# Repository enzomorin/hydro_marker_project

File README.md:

# hydro_marker_project

A beacon placed in small rivers to measure flooding risk, hydric stress, or normal conditions — built for the **Olympiads of Engineering Sciences**.

---

## Project overview

Each marker is a waterproof device deployed in a river. It measures water level, pressure, temperature, and battery voltage, then transmits the data via radio to a ground antenna. The antenna forwards the data to the API server, which stores it and makes it available to a dashboard and a mobile alert application.

---

## Repository structure

```
hydro_marker_project/
│
├── docs/           Documentation, source references, notes, and diagrams
│
├── app/            Dashboard application
│                   Receives data from the ground antenna, processes it,
│                   and sends it to the API. Also includes a companion app
│                   that sends alerts when a nearby marker detects potential
│                   flooding or hydric stress.
│
├── firmware/       Embedded code
│                   MCU code for the marker (sensor reading + radio transmission)
│                   and code for the ground station (receiving + forwarding frames).
│
├── hardware/       PCB design files (KiCad)
│                   Optimised circuit board for the markers — reduces electrical
│                   noise and improves efficiency.
│
├── server/         API server
│                   FastAPI + SQLite REST API that stores marker locations
│                   and all associated measurement data.
│
├── site/           Promotional website
│                   Presents the product and its specifications.
│                   Also displays live marker data and locations on a map.
│
└── tools/          Development utilities
                    Scripts and helpers that speed up development across
                    all parts of the project.
```

---

## Quick start

To run the API server locally, see [`server/README.md`](server/README.md).

---

## Tech used overview

| Component | Technology |
|---|---|
| API server | Python, FastAPI, SQLite |
| Firmware | C++ (MCU), PlatfromIO IDE |
| PCB design | KiCad |
| Dashboard | Electron, Javascript |
| Website | HTML, CSS, Javascript |

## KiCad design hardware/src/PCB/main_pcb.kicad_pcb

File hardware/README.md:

# HydroVinci — PCB Design

> Compact, low-power PCB for the HydroVinci marker system. Designed in KiCad 10, built around the Seeed XIAO nRF52840 Plus.

---

## Table of Contents

- [Overview](#overview)
- [Hardware Summary](#hardware-summary)
- [Prerequisites](#prerequisites)
- [Opening the Project](#opening-the-project)
- [Manufacturing](#manufacturing)
- [Design Notes](#design-notes)
- [Tech used](#tech-used)

---

## Overview

This repository contains the full KiCad design files for the HydroVinci PCB. The board integrates all electronics required by the marker into a single compact PCB, replacing a wired prototype with a manufacturable solution.

The design targets low quiescent current for battery-powered field deployment, with switchable power rails for each peripheral.

---

## Hardware Summary

| Component | Description |
|-----------|-------------|
| MCU | Seeed XIAO nRF52840 Plus (BLE 5.0, nRF52840) |
| Power | LiPo battery input, 12V boost (Adafruit TPS61040) |
| Pressure sensor | DFRobot KIT0139 submersible 4-20mA, converted via SEN0262 |
| Environmental | AZ-Delivery GY-BME280 (temperature, humidity, pressure) |
| Hall effect | Digital Hall sensor via BSS84 high-side switch |
| Data logging | SparkFun OpenLog DEV-13712 (microSD, UART) |
| RF | CC1101 sub-GHz radio module |
| Power switching | BSS138 + BSS84 MOSFET pairs (3.3V and 12V rails) |
| Indicators | Passive buzzer, 2× tactile buttons |

---

## Prerequisites

- [KiCad](https://www.kicad.org/) `>= 10.0`

No additional dependencies. All custom symbols and footprints are included in the repository under `src/PCB/libraries/`.

---

## Opening the Project

1. Clone the repository
   ```bash
   git clone https://github.com/your-org/hydrovinci-pcb.git
   ```

2. Open KiCad and select **File → Open Project**

3. Navigate to `src/PCB/main_pcb.kicad_pro` and open it

From the KiCad project manager you can then open:
- **Schematic Editor** — for the electrical design and component wiring
- **PCB Editor** — for the physical board layout and copper routing

---

## Manufacturing

Gerber files are required to manufacture the board. To generate them from KiCad:

1. Open the PCB Editor (`main_pcb.kicad_pcb`)
2. Go to **File → Fabrication Outputs → Gerbers**
3. Select all required layers and export

The generated Gerbers can be uploaded directly to:
- [JLCPCB](https://jlcpcb.com) — recommended for low-cost prototyping
- [PCBway](https://www.pcbway.com) — recommended for higher quantities

> **Recommended specs:** 2-layer, 1oz copper.

---

## Design Notes

- All GPIO outputs include 100Ω series resistors for noise immunity
- The 12V rail (KIT0139 sensor loop) is switched via a BSS138 + BSS84 MOSFET pair — Vgs is clamped to −6V by R20 to stay within BSS84 absolute maximum ratings
- The EN pin of the boost converter is pulled to GND via R7 (100kΩ) to ensure the 12V rail is off during boot and reset
- The SEN0262 output capacitor (C14) must be rated ≥ 25V (ceramic X5R/X7R, 0805)
- I2C pull-ups R3/R4 (10kΩ) may be omitted if the BME280 module already includes them

---

## Tech used

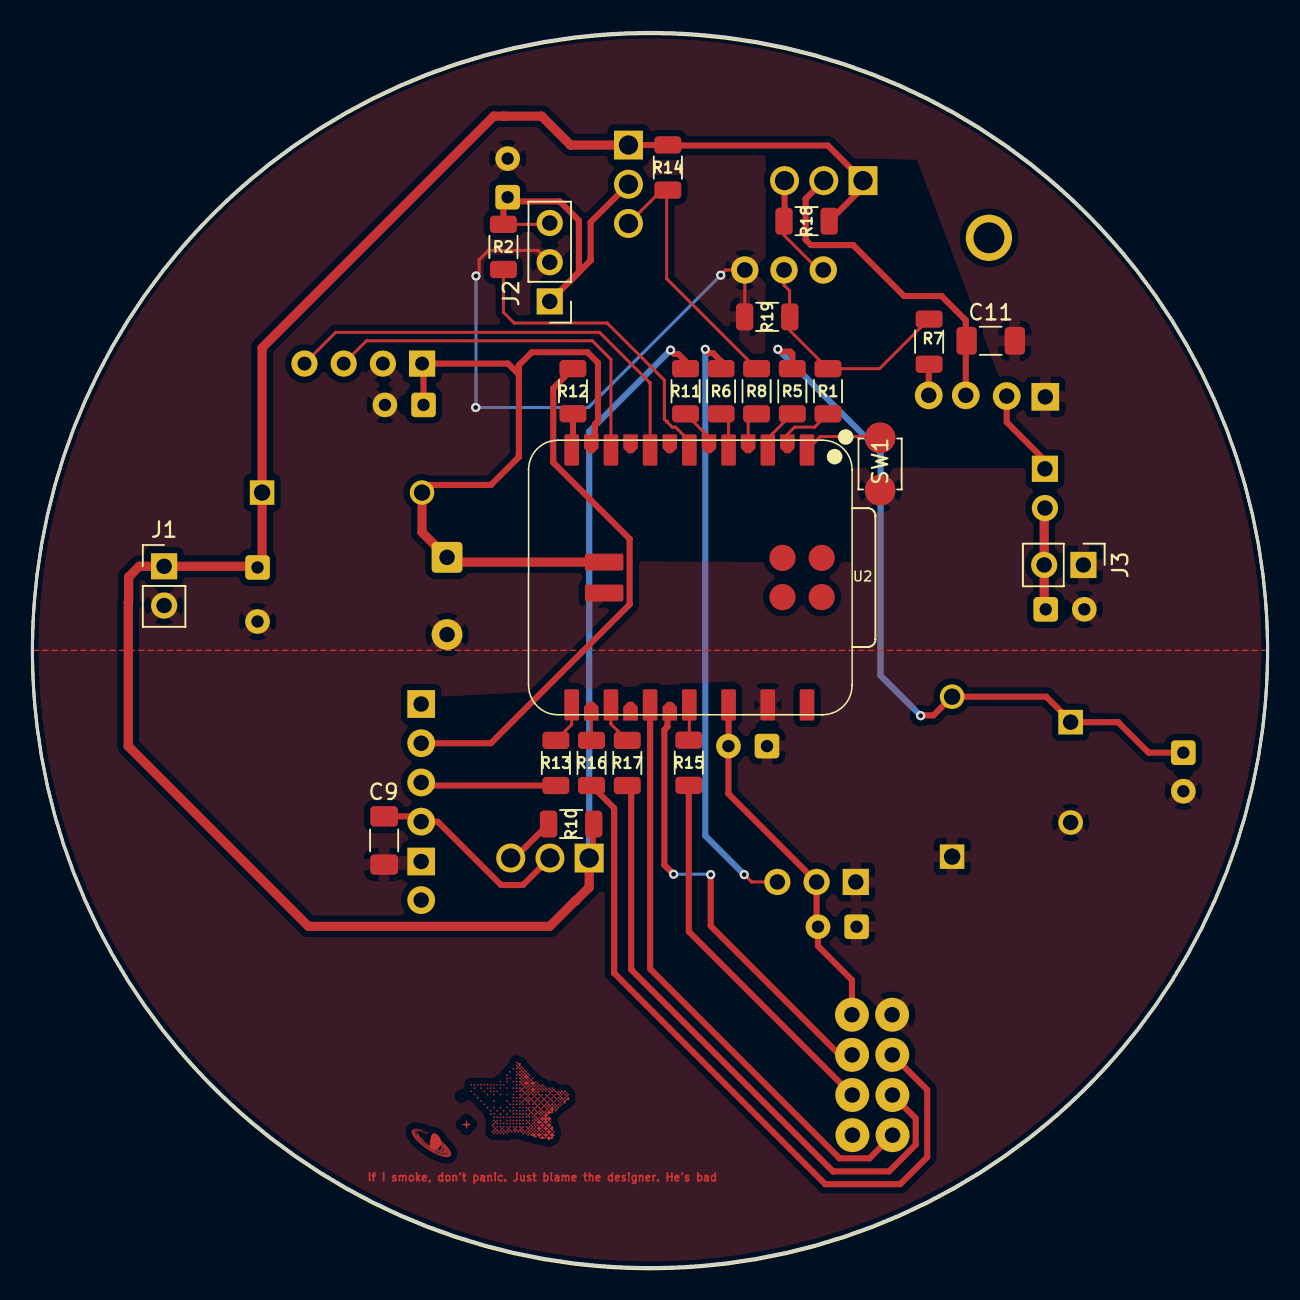
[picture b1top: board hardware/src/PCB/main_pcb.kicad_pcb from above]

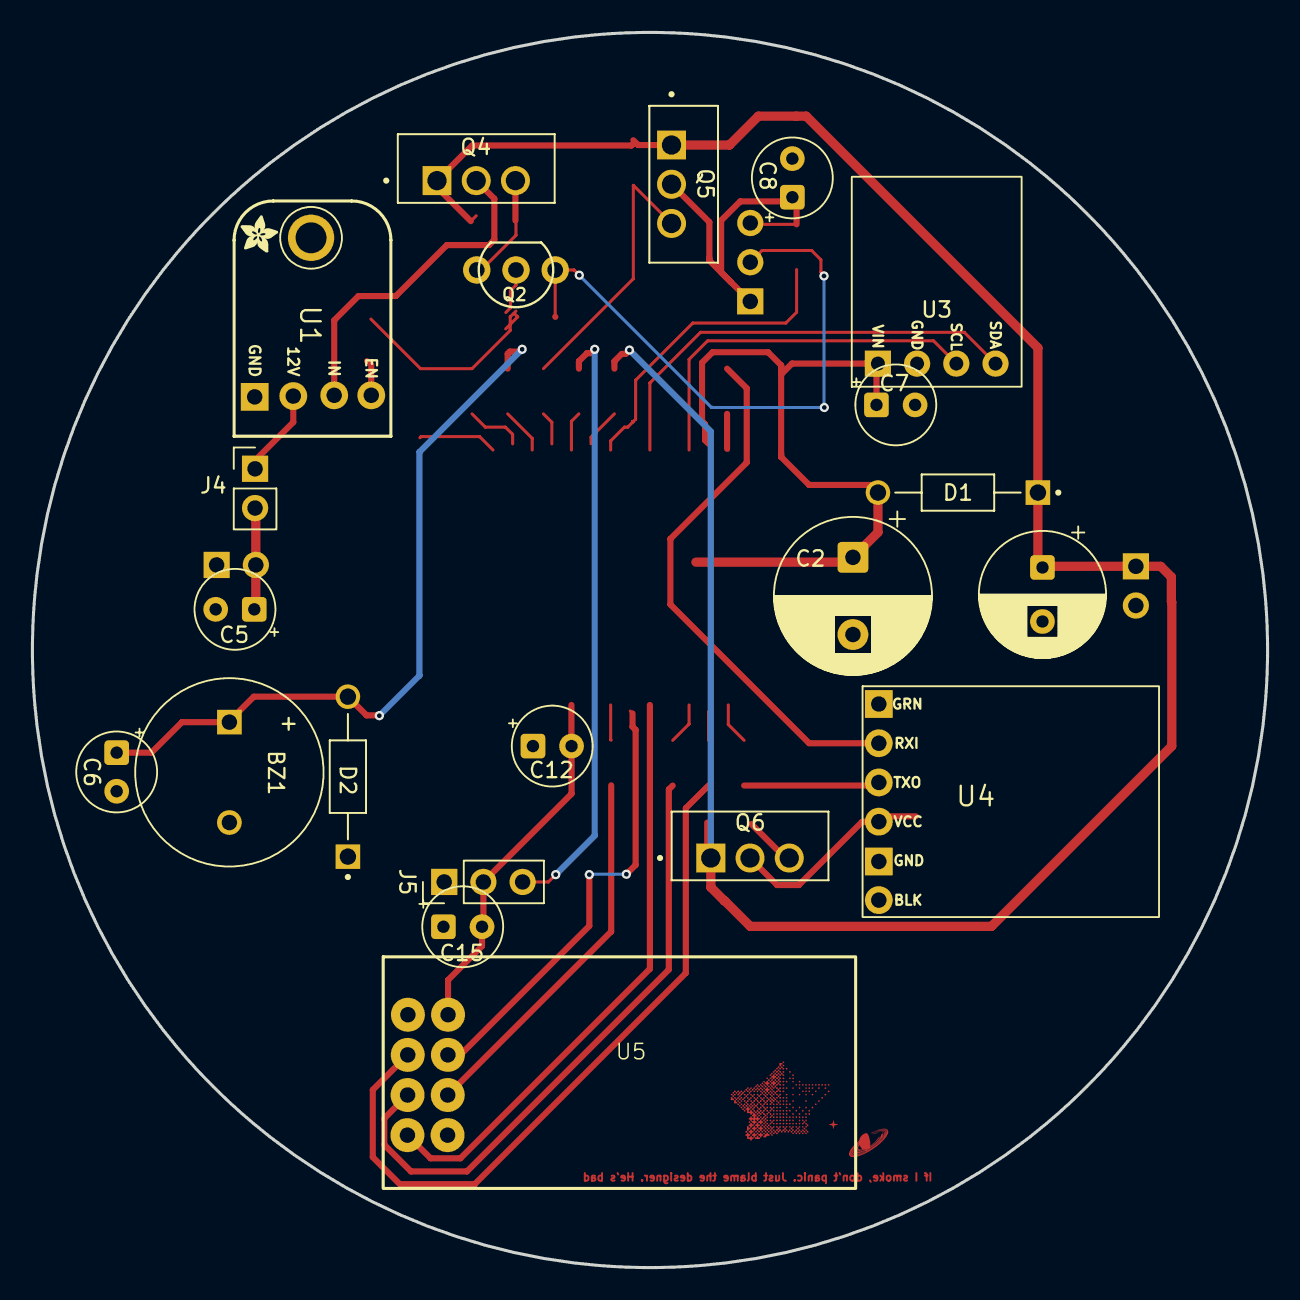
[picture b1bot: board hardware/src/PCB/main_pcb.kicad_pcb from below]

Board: 2 copper layers, 80.0 x 80.0 mm, 44 parts (21 on the bottom side), 30 nets.

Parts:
BZ1: Buzzer; MagneticBuzzer_ProSignal_ABT-410-RC
C2: 47 µF - électrolytique; CP_Radial_D10.0mm_P5.00mm
C5, C6, C7, C8, C12, C15: 100 nF - céramique; CP_Radial_Tantal_D5.0mm_P2.50mm
C9, C11: 100 nF - céramique; C_1206_3216Metric_Pad1.33x1.80mm_HandSolder
C17: 220 µF - électrolytique; CP_Radial_D8.0mm_P3.50mm
D1: 1N5819; DIOAD1036W78L470D235
D2: fr107; DIOAD1036W78L470D235
J1: Batt; PinHeader_1x02_P2.54mm_Vertical
J2: Hall_sensor; PinHeader_1x03_P2.54mm_Vertical
J3: Pressure_sensor; PinHeader_1x02_P2.54mm_Vertical
J4: Pressure_pins; PinHeader_1x02_P2.54mm_Vertical
J5: converter_pins; PinHeader_1x03_P2.54mm_Vertical
Q2: BS170; TO92
Q4, Q5, Q6: IRF9530; TRANS_IRF9530
R1, R5, R8, R11, R12, R13: 100 Ω; R_1206_3216Metric
R2: 10k Ω; R_1206_3216Metric
R6: 1k Ω; R_1206_3216Metric
R7, R10, R14, R18, R19: 100k Ω; R_1206_3216Metric
R15, R16, R17: 33 Ω; R_1206_3216Metric
SW1: Button; SW_SPST_B3U-1000P
U1: Adafruit_TPS61040_5644
U2: XIAO-nRF52840-Plus-SMD
U3: BME280
U4: OpenLog
U5: CC1101

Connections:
+3.3V: BZ1.1 (+), C2.1, C6.1, C7.1, C8.1, C9.1, C11.1, C12.2, C15.2, C17.1, D1.A, D1.C, D2.A, J1.1, J2.1, J2.3, J5.2, Q4.1 (G), Q4.2 (S), Q5.2 (S), Q5.3 (D), Q6.2 (S), Q6.3 (D), R2.1, R5.1, R10.2, R14.2, R18.2, U1.1 (vcc), U2.12 (3V3), U2.28, U3.1 (vcc), U4.4 (vcc), U5.2 (VCC)
+12V: C5.1, J3.2, J4.1, J4.2, U1.3 (Vout)
/Button: SW1.1 (A), U2.1 (P0.02_A0_D0)
/Hall: R2.2, U2.4 (P0.29_A3_D3)
/MISO1: U2.10 (P1.14_D9_MISO), U5.7 (MISO)
/MOSFET2: Q5.1 (G), R8.1, R14.1
/MOSFET3: Q6.1 (G), R10.1, R11.1
/MOSI1: R15.1, U5.6 (MOSI)
/PressureA: J5.3, R6.1
/RF_CSN: U2.23 (P1.07_D19_MOSI1), U5.4 (CSN)
/RF_GDO0: R16.1, U5.3 (GDO0)
/SCK1: R17.1, U5.5 (SCK)
/SCL1: U2.6 (P0.05_A5_D5_SCL), U3.3 (scl)
/SDA1: U2.5 (P0.04_A4_D4_SDA), U3.4 (sda)
/SD_RX: R12.1, U4.2 (rxi)
/SD_TX: R13.1, U4.3 (txo)
/Transistor+: Q2.3 (D), Q4.3 (D), R18.1
GND: BZ1.2 (-), C2.2, C5.2, C6.2, C7.2, C8.2, C9.2, C11.2, C12.1, C15.1, C17.2, D2.C, J1.2, J2.2, J3.1, J5.1, Q2.1 (G), R7.2, R19.1, SW1.2 (A), U1.2 (gnd), U2.13 (GND), U2.29, U3.2 (gnd), U4.5 (gnd), U5.1 (GND)
unnamed: Q2.2 (S), R1.1, R19.2
unnamed: R7.1, U1.4 (en_(enable))
unnamed: R5.2, U2.2 (P0.03_A1_D1)
unnamed: R1.2, U2.15 (P0.15_D11_I2S_SD)
unnamed: R8.2, U2.16 (P0.19_D12_I2S_SCK)
unnamed: R6.2, U2.3 (P0.28_A2_D2)
unnamed: R11.2, U2.17 (P1.01_D13_I2S_WS)
unnamed: R16.2, U2.21 (P1.03_D17_SCK1)
unnamed: R12.2, U2.7 (P1.11_D6_TX)
unnamed: R13.2, U2.8 (P1.12_D7_RX)
unnamed: R17.2, U2.9 (P1.13_D8_SCK)
unnamed: R15.2, U2.11 (P1.15_D10_MOSI)

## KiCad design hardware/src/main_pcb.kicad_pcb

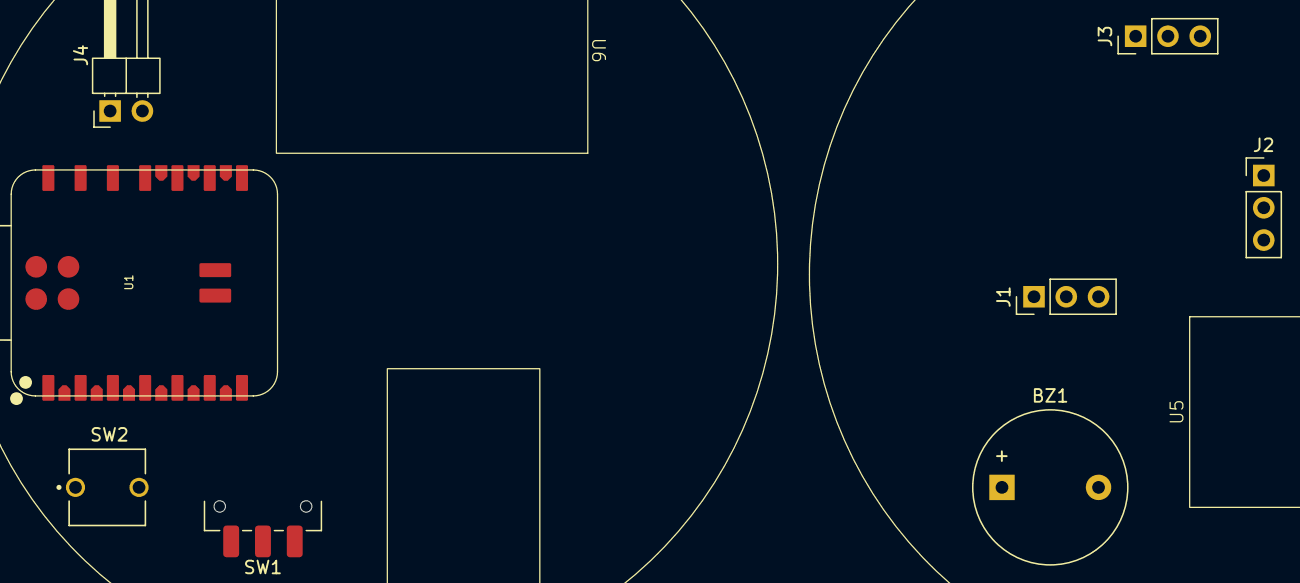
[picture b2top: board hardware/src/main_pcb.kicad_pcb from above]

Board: 2 copper layers, 11 parts (0 on the bottom side), 4 nets, no tracks yet.

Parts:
BZ1: Buzzer_info; Buzzer_12x9.5RM7.6
J1: Servo_motor; PinHeader_1x03_P2.54mm_Vertical
J2: Sen057_pressure_sensor; PinHeader_1x03_P2.54mm_Vertical
J3: Hall_effect_sensor; PinHeader_1x03_P2.54mm_Vertical
J4: Jack plug; PinHeader_1x02_P2.54mm_Horizontal
SW1: SPDT_Slide_SMD_6.7x2.6mm; SW_SPDT_CK_JS102011SAQN
SW2: telemetry_btn; SW_BUTT-2
U1: XIAO-nRF52840-Plus-SMD
U2: 5V_booster
U5: Openlog_SDcard; Openlog_SDreader
U6: Radio_module; Ebyte_radio_module

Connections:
+3.3V: J3.2, U1.12 (3V3)
+5V: J1.2, J2.2, SW1.1 (A), U1.14 (VBUS)
/Btn: SW2.1 (A), SW2.2 (A), U1.1 (P0.02_A0_D0)
GND: BZ1.2 (-), J1.3, J2.3, J3.3, J4.2, SW1.3 (C), U1.13 (GND), U1.27 (GND)

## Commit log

2026-04-09 docs pour se connard d'andrea (daito_pussy_licker_93)
2026-04-10 init: starting project
2026-04-16 feature: conso analysis
2026-04-16 feature: CSS generator init
2026-04-17 feature: API - server + cleaning
2026-04-17 feature: PCB cleaner(perfect🤤)
2026-04-19 feature: PCB advancement
2026-04-19 feature: a bit of cleaning
2026-04-20 feature: PCB advancement
2026-05-03 feature: PCB finished finally AAAAAAAAAAAAAAAAAAAAH
2026-05-03 feature: PCB ready to manufacture
2026-05-04 feature: PCB ready to manufacture and firmeware start
2026-05-04 feature: A bit of style
